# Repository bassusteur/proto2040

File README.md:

# This is proto2040, an rp2040 based board.

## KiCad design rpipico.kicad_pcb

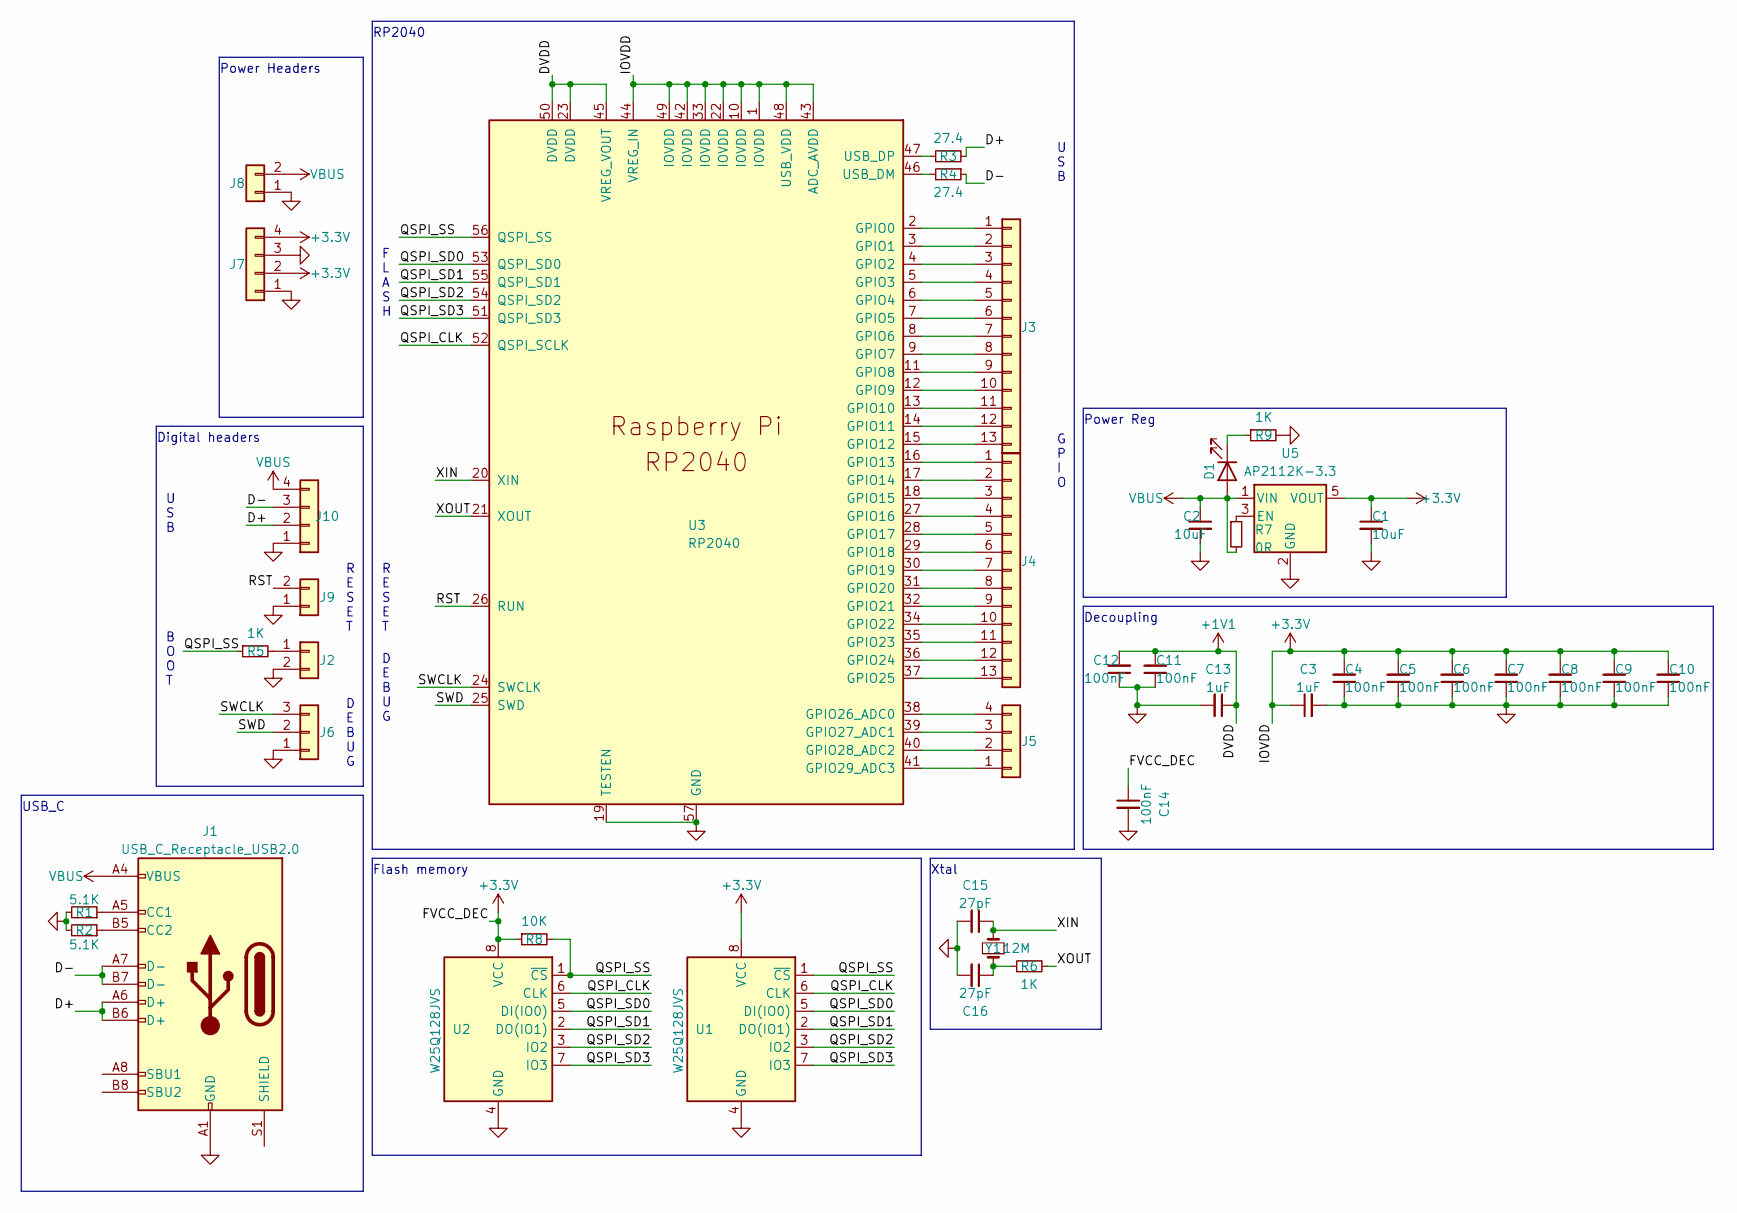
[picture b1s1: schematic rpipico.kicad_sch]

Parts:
C1, C2: 10uF; C_0402_1005Metric
C3, C13: 1uF; C_0201_0603Metric
C4, C5, C6, C7, C8, C9, C10, C11, C12, C14: 100nF; C_0201_0603Metric
C15, C16: 27pF; C_0201_0603Metric
D1: LED; LED_0603_1608Metric
J1: USB_C_Receptacle_USB2.0; USB_C_Receptacle_G-Switch_GT-USB-7010ASV
J2, J9: Conn_01x02; PinHeader_1x02_P1.00mm_Vertical
J3, J4: Conn_01x13; PinHeader_1x13_P1.00mm_Vertical
J5, J10: Conn_01x04; PinHeader_1x04_P1.00mm_Vertical
J6: Conn_01x03; PinHeader_1x03_P1.27mm_Vertical
J7: Conn_01x04; PinHeader_1x04_P1.27mm_Vertical
J8: Conn_01x02; PinHeader_1x02_P1.27mm_Vertical
R1, R2: 5.1K; R_0402_1005Metric
R3, R4: 27.4; R_0402_1005Metric
R5, R9: 1K; R_0402_1005Metric
R6: 1K; R_0201_0603Metric
R7: 0R
R8: 10K; R_0402_1005Metric
U1: W25Q128JVS; DFN-8-1EP_3x2mm_P0.5mm_EP1.3x1.5mm
U2: W25Q128JVS; SOIC-8_5.23x5.23mm_P1.27mm
U3: RP2040; RP2040-QFN-56
U5: AP2112K-3.3; SOT-23-5
Y1: 12M; Crystal_SMD_3225-4Pin_3.2x2.5mm

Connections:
+1V1: C11.2, C12.2, C13.1, U3.23 (DVDD), U3.45 (VREG_VOUT), U3.50 (DVDD)
+3.3V: C1.1, C3.1, C4.2, C5.2, C6.2, C7.2, C8.2, C9.2, C10.2, C14.1, J7.2, J7.4, R8.1, U1.8 (VCC), U2.8 (VCC), U3.1 (IOVDD), U3.10 (IOVDD), U3.22 (IOVDD), U3.33 (IOVDD), U3.42 (IOVDD), U3.43 (ADC_AVDD), U3.44 (VREG_IN), U3.48 (USB_VDD), U3.49 (IOVDD), U5.5 (VOUT)
/D+: J1.A6 (D+), J1.B6 (D+), J10.2, R3.2
/D-: J1.A7 (D-), J1.B7 (D-), J10.3, R4.1
/QSPI_CLK: U1.6 (CLK), U2.6 (CLK), U3.52 (QSPI_SCLK)
/QSPI_SD0: U1.5 (DI(IO0)), U2.5 (DI(IO0)), U3.53 (QSPI_SD0)
/QSPI_SD1: U1.2 (DO(IO1)), U2.2 (DO(IO1)), U3.55 (QSPI_SD1)
/QSPI_SD2: U1.3 (IO2), U2.3 (IO2), U3.54 (QSPI_SD2)
/QSPI_SD3: U1.7 (IO3), U2.7 (IO3), U3.51 (QSPI_SD3)
/QSPI_SS: R5.1, R8.2, U1.1 (~CS), U2.1 (~CS), U3.56 (QSPI_SS)
/RST: J9.2, U3.26 (RUN)
/SWCLK: J6.3, U3.24 (SWCLK)
/SWD: J6.2, U3.25 (SWD)
/XIN: C15.1, U3.20 (XIN), Y1.2
/XOUT: R6.2, U3.21 (XOUT)
GND: C1.2, C2.2, C3.2, C4.1, C5.1, C6.1, C7.1, C8.1, C9.1, C10.1, C11.1, C12.1, C13.2, C14.2, C15.2, C16.2, J1.A1 (GND), J1.A12 (GND), J1.B1 (GND), J1.B12 (GND), J2.2, J6.1, J7.1, J7.3, J8.1, J9.1, J10.1, R1.2, R2.2, R9.2, U1.4 (GND), U2.4 (GND), U3.19 (TESTEN), U3.57 (GND), U5.2 (GND)
unnamed: C16.1, R6.1, Y1.1
unnamed: D1.1 (K), R9.1
unnamed: J1.A5 (CC1), R1.1
unnamed: J1.B5 (CC2), R2.1
unnamed: J2.1, R5.2
unnamed: J3.1, U3.2 (GPIO0)
unnamed: J3.2, U3.3 (GPIO1)
unnamed: J3.3, U3.4 (GPIO2)
unnamed: J3.4, U3.5 (GPIO3)
unnamed: J3.5, U3.6 (GPIO4)
unnamed: J3.6, U3.7 (GPIO5)
unnamed: J3.7, U3.8 (GPIO6)
unnamed: J3.8, U3.9 (GPIO7)
unnamed: J3.9, U3.11 (GPIO8)
unnamed: J3.10, U3.12 (GPIO9)
unnamed: J3.11, U3.13 (GPIO10)
unnamed: J3.12, U3.14 (GPIO11)
unnamed: J3.13, U3.15 (GPIO12)
unnamed: J4.1, U3.16 (GPIO13)
unnamed: J4.2, U3.17 (GPIO14)
unnamed: J4.3, U3.18 (GPIO15)
unnamed: J4.4, U3.27 (GPIO16)
unnamed: J4.5, U3.28 (GPIO17)
unnamed: J4.6, U3.29 (GPIO18)
unnamed: J4.7, U3.30 (GPIO19)
unnamed: J4.8, U3.31 (GPIO20)
unnamed: J4.9, U3.32 (GPIO21)
unnamed: J4.10, U3.34 (GPIO22)
unnamed: J4.11, U3.35 (GPIO23)
unnamed: J4.12, U3.36 (GPIO24)
unnamed: J4.13, U3.37 (GPIO25)
unnamed: J5.1, U3.41 (GPIO29_ADC3)
unnamed: J5.2, U3.40 (GPIO28_ADC2)
unnamed: J5.3, U3.39 (GPIO27_ADC1)
unnamed: J5.4, U3.38 (GPIO26_ADC0)
unnamed: R4.2, U3.46 (USB_DM)
unnamed: R3.1, U3.47 (USB_DP)
unnamed: R7.1, U5.3 (EN)
VBUS: C2.1, D1.2 (A), J1.A4 (VBUS), J1.A9 (VBUS), J1.B4 (VBUS), J1.B9 (VBUS), J8.2, J10.4, R7.2, U5.1 (VIN)

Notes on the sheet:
RP2040
G P I O
Flash memory
U S B
R E S E T
USB_C
Power Headers
Power Reg
B O O T
Xtal
Digital headers
Decoupling
D E B U G
F L A S H

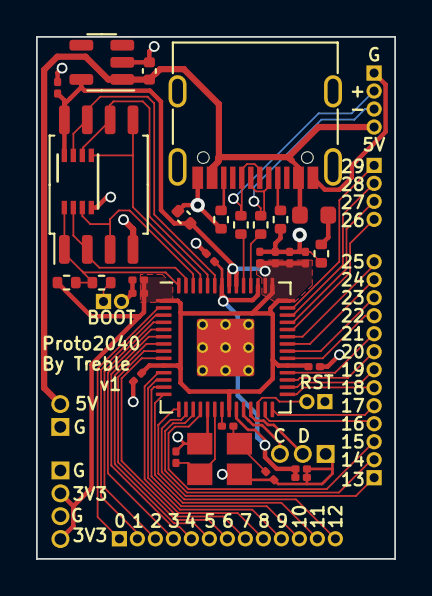
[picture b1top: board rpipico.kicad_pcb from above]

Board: 2 copper layers, 19.9 x 29.0 mm, 40 parts (0 on the bottom side), 54 nets.
